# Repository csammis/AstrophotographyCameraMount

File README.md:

# Astrophotography Camera Mount

This project is documented on [Hackaday.io](https://hackaday.io/project/163689-astrophotography-camera-mount)!

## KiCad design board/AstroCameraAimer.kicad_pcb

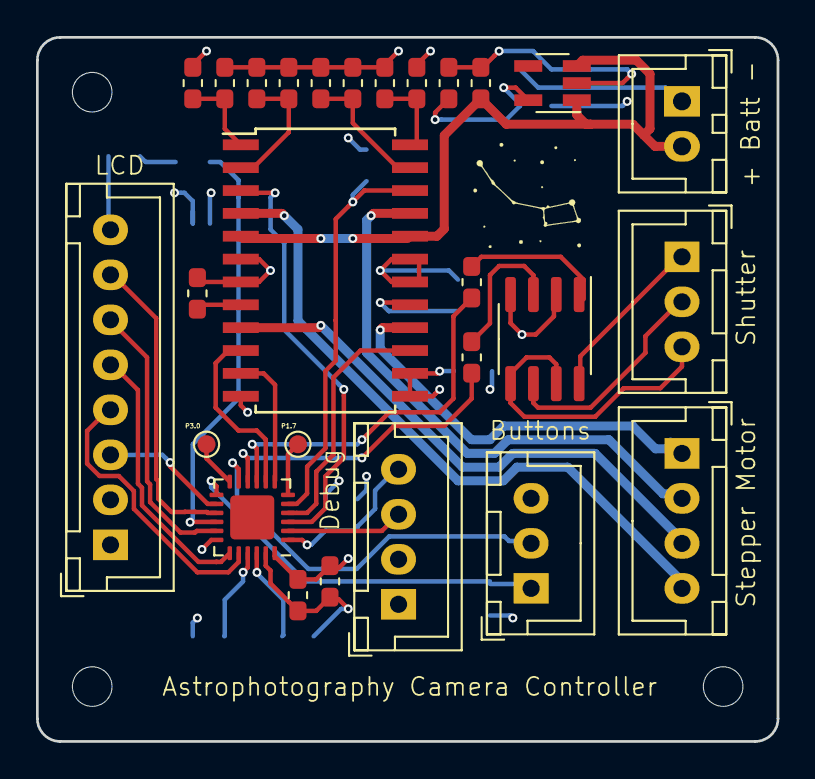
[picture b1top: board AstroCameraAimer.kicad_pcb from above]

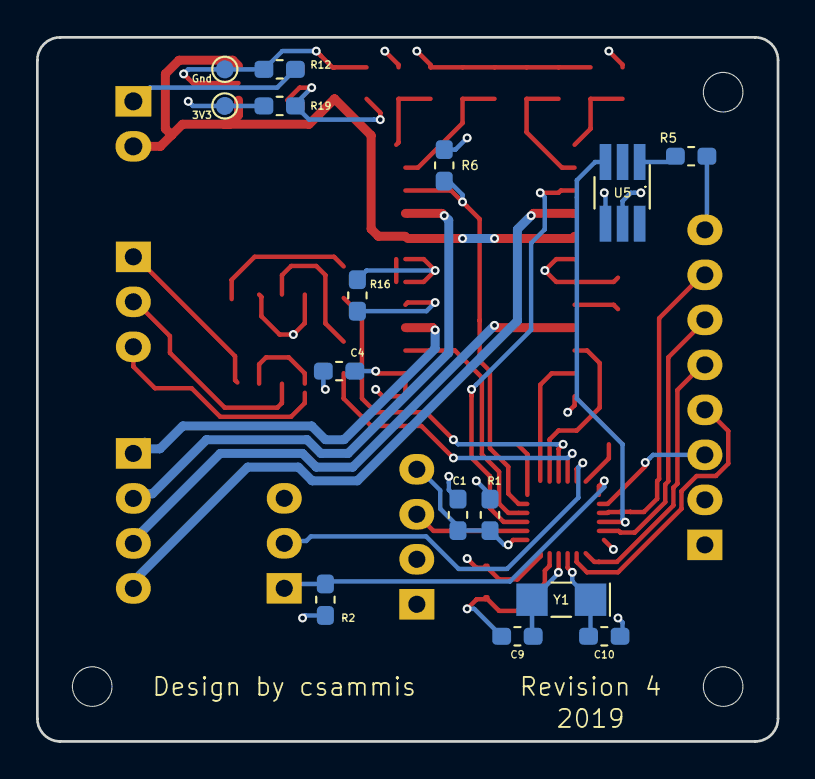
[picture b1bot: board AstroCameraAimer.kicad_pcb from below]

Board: 4 copper layers, 41.1 x 39.1 mm, 46 parts (15 on the bottom side), 43 nets.

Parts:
C1: 1nF; C_0603_1608Metric_Pad1.05x0.95mm_HandSolder
C2: 10uF; C_0603_1608Metric_Pad1.05x0.95mm_HandSolder
C3: 0.1uF; C_0603_1608Metric_Pad1.05x0.95mm_HandSolder
C4, C11, C12: 1uF; C_0603_1608Metric_Pad1.05x0.95mm_HandSolder
C7, C8: 68pF; C_0603_1608Metric_Pad1.05x0.95mm_HandSolder
C9: CL1; C_0603_1608Metric_Pad1.05x0.95mm_HandSolder
C10: CL2; C_0603_1608Metric_Pad1.05x0.95mm_HandSolder
H1, H2, H3: M2; MountingHole_2.2mm_M2
J1: SBW; JST_XH_B04B-XH-A_1x04_P2.50mm_Vertical
J2: Shutter; JST_XH_B03B-XH-A_1x03_P2.50mm_Vertical
J3: LCD; JST_XH_B08B-XH-A_1x08_P2.50mm_Vertical
J4: Battery; JST_XH_B02B-XH-A_1x02_P2.50mm_Vertical
J5: Stepper Motor; JST_XH_B04B-XH-A_1x04_P2.50mm_Vertical
J6: Buttons; JST_XH_B03B-XH-A_1x03_P2.50mm_Vertical
LG1: ProjectLogo; ursa_minor
R1: 47K; R_0603_1608Metric_Pad1.05x0.95mm_HandSolder
R2, R6, R10: 100K; R_0603_1608Metric_Pad1.05x0.95mm_HandSolder
R3, R4, R5: 390; R_0603_1608Metric_Pad1.05x0.95mm_HandSolder
R8: 13K; R_0603_1608Metric_Pad1.05x0.95mm_HandSolder
R9, R15, R20: 20K; R_0603_1608Metric_Pad1.05x0.95mm_HandSolder
R11: 68K; R_0603_1608Metric_Pad1.05x0.95mm_HandSolder
R12, R19: JUMPER; R_0603_1608Metric_Pad1.05x0.95mm_HandSolder
R16, R17: 0.75Ω; R_0603_1608Metric_Pad1.05x0.95mm_HandSolder
TP1: GND; TestPoint_Pad_D1.0mm
TP2: 3.3V; TestPoint_Pad_D1.0mm
TP3: P3.0; TestPoint_Pad_D1.0mm
TP4: P1.7; TestPoint_Pad_D1.0mm
U1: MSP430FR2433; VQFN-24-1EP_4x4mm_P0.5mm_EP2.45x2.45mm
U2: ILD205; SOIC-8_3.9x4.9mm_P1.27mm
U3: A3967; SOIC-24W_7.5x15.4mm_P1.27mm
U4: NCP718; SOT-23-5_HandSoldering
U5: SiP32510; TSOT-23-6_HandSoldering
Y1: 32Khz; Crystal_SMD_MicroCrystal_CC7V-T1A-2Pin_3.2x1.5mm_HandSolder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

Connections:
+3V3: C2.1, C3.2, C4.2, J1.2, J3.1, R1.1, R2.1, R6.1, R8.1, R10.1, R19.1, TP2.1, U1.24, U3.12, U3.13, U3.14, U5.5
/9V_Coil1A: J5.1, U3.16
/9V_Coil1B: J5.2, U3.21
/9V_Coil2A: J5.3, U3.9
/9V_Coil2B: J5.4, U3.4
/LCD_CLK: J3.7, U1.15
/LCD_DC: J3.5, U1.19
/LCD_MOSI: J3.6, U1.17
/LCD_RST: J3.4, U1.20
/LCD_nCS: J3.3, U1.14
BATT_9V: C11.1, J4.2, U3.5, U3.20, U4.1, U4.3
DRIVER_DIR: U1.7, U3.11
DRIVER_STEP: U1.8, U3.10
DRIVER_nENABLE: U1.4, U3.15
DRIVER_nRESET: R6.2, U1.5, U3.22
DRIVER_nSLEEP: U1.3, U3.3
FOCUS: R3.2, U1.9
GND: C1.2, C2.2, C3.1, C4.1, C7.1, C8.1, C9.2, C10.2, C11.2, C12.2, J1.1, J3.2, J6.3, R9.1, R11.2, R12.2, R15.2, R16.1, R17.1, R20.2, TP1.1, U1.18, U1.23, U2.2, U2.4, U3.6, U3.7, U3.18, U3.19, U4.2, U5.4
LCD_LED: U1.16, U5.3
unnamed: C1.1, J1.4, R1.2, U1.1
unnamed: C7.2, R15.1, U3.2
unnamed: C8.2, R20.1, U3.23
unnamed: C9.1, U1.22, Y1.2
unnamed: C10.1, U1.21, Y1.1
unnamed: J1.3, U1.2
unnamed: J2.1, U2.8
unnamed: J2.2, U2.6
unnamed: J2.3, U2.5, U2.7
unnamed: J3.8, R5.1
unnamed: J4.1, R12.1
unnamed: R3.1, U2.1
unnamed: R4.1, U2.3
unnamed: R5.2, U5.1
unnamed: R8.2, R9.2, U3.1
unnamed: R10.2, R11.1, U3.24
unnamed: R16.2, U3.17
unnamed: R17.2, U3.8
unnamed: TP3.1, U1.12
unnamed: TP4.1, U1.6
OK_BTN: J6.1, R2.2, U1.13
SELECT_BTN: J6.2, U1.11
SHUTTER: R4.2, U1.10
SUPPLY_3.3V: C12.1, R19.2, U4.5

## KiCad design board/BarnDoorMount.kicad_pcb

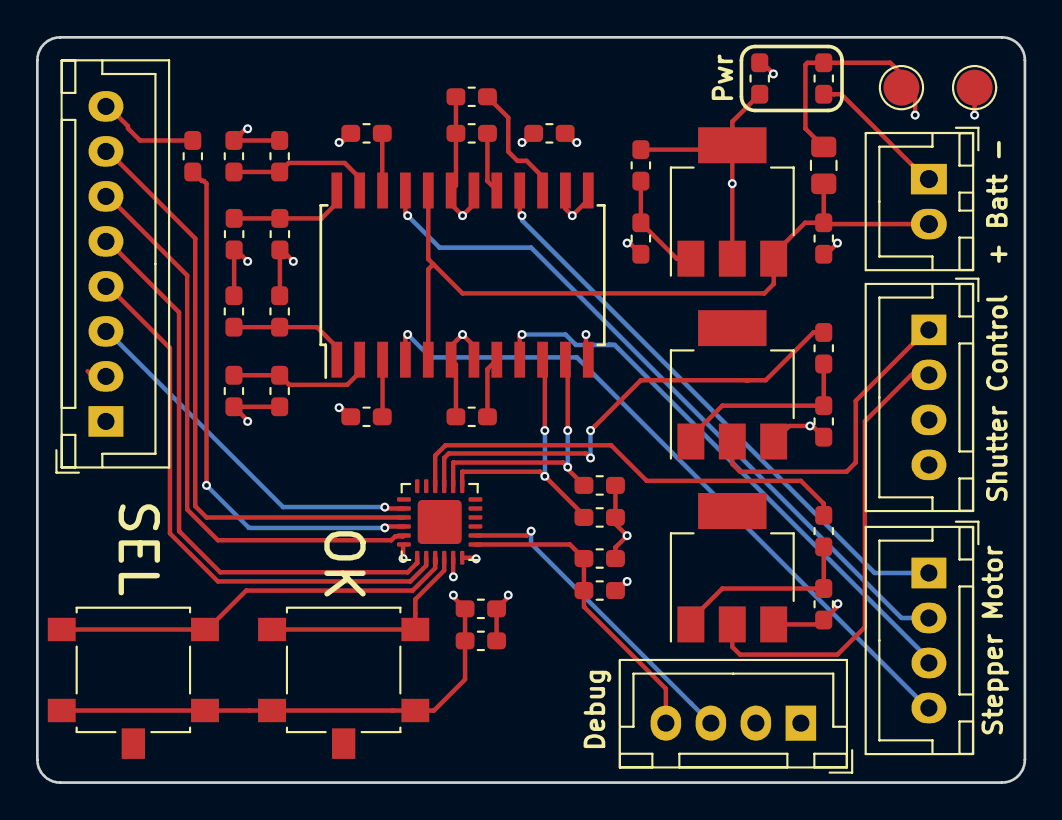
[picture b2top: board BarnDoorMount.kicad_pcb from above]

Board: 4 copper layers, 54.9 x 41.4 mm, 45 parts (0 on the bottom side), 38 nets.

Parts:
+ C5: 47uF; C_0805_2012Metric_Pad1.15x1.40mm_HandSolder
C1: 1nF; C_0603_1608Metric_Pad1.05x0.95mm_HandSolder
C2 +: 10uF; C_0603_1608Metric_Pad1.05x0.95mm_HandSolder
C3, C6: 0.1uF; C_0603_1608Metric_Pad1.05x0.95mm_HandSolder
C4: 1uF; C_0603_1608Metric_Pad1.05x0.95mm_HandSolder
C7, C8: 68pF; C_0603_1608Metric_Pad1.05x0.95mm_HandSolder
J1: SBW; JST_XH_B04B-XH-A_1x04_P2.50mm_Vertical
J2: Shutter Control; JST_XH_B04B-XH-A_1x04_P2.50mm_Vertical
J3: LCD; JST_XH_B08B-XH-A_1x08_P2.50mm_Vertical
J4: Battery; JST_XH_B02B-XH-A_1x02_P2.50mm_Vertical
J5: Stepper Motor; JST_XH_B04B-XH-A_1x04_P2.50mm_Vertical
Q1, Q2: PZT2222A; SOT-223
R1: 47K; R_0603_1608Metric_Pad1.05x0.95mm_HandSolder
R2, R3, R8, R16, R17, R18, R19, R20: 10K; R_0603_1608Metric_Pad1.05x0.95mm_HandSolder
R4, R5: 1K; R_0603_1608Metric_Pad1.05x0.95mm_HandSolder
R6, R11, R15: 20K; R_0603_1608Metric_Pad1.05x0.95mm_HandSolder
R7: 13K; R_0603_1608Metric_Pad1.05x0.95mm_HandSolder
R9: 6.8K; R_0603_1608Metric_Pad1.05x0.95mm_HandSolder
R10, R23: 390; R_0603_1608Metric_Pad1.05x0.95mm_HandSolder
R12, R13: 0.75; R_0603_1608Metric_Pad1.05x0.95mm_HandSolder
R14: 240; R_0603_1608Metric_Pad1.05x0.95mm_HandSolder
R21, R22: JUMPER; R_0603_1608Metric_Pad1.05x0.95mm_HandSolder
SW1: SELECT; SW_SPST_B3S-1100
SW2: OK; SW_SPST_B3S-1100
TP1: TP_GND; TestPoint_Pad_D2.0mm
TP2: TP_33V; TestPoint_Pad_D2.0mm
U1: MSP430FR2433; VQFN-24-1EP_4x4mm_P0.5mm_EP2.45x2.45mm
U2: LM317; SOT-223-3_TabPin2
U3: A3967; SOIC-24W_7.5x15.4mm_P1.27mm

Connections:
+3V3: C2 +.1, C3.2, C4.1, J1.2, J3.1, R1.1, R7.1, R8.1, R18.1, R19.1, R22.1, TP2.1, U1.24, U3.12, U3.13, U3.14
+9V: + C5.1, C6.1, J4.2, U2.3, U3.5, U3.20
FOCUS: R2.2, U1.9
GND: + C5.2, C1.2, C2 +.2, C3.1, C4.2, C6.2, C7.2, C8.2, J1.1, J2.3, J3.2, Q1.3, Q2.3, R4.1, R5.1, R6.1, R9.2, R10.2, R11.2, R12.1, R13.1, R15.2, R16.2, R17.2, R20.1, R21.2, SW1.2, SW2.2, TP1.1, U1.18, U1.23, U3.6, U3.7, U3.18, U3.19
unnamed: C1.1, J1.4, R1.2, U1.1
unnamed: C7.1, R11.1, U3.2
unnamed: C8.1, R15.1, U3.23
unnamed: J1.3, U1.2
unnamed: J2.1, Q1.2
unnamed: J2.2, Q2.2
unnamed: J3.3, U1.14
unnamed: J3.4, U1.20
unnamed: J3.5, U1.19
unnamed: J3.6, U1.17
unnamed: J3.7, U1.15
unnamed: J3.8, R23.2
unnamed: J4.1, R21.1
unnamed: J5.1, U3.16
unnamed: J5.2, U3.21
unnamed: J5.3, U3.9
unnamed: J5.4, U3.4
unnamed: Q1.1, R2.1, R4.2
unnamed: Q2.1, R3.1, R5.2
unnamed: R6.2, R7.2, U3.1
unnamed: R8.2, R9.1, U3.24
unnamed: R10.1, R14.2, U2.1
unnamed: R12.2, U3.17
unnamed: R13.2, U3.8
unnamed: R14.1, R22.2, U2.2
unnamed: R16.1, U1.8, U3.11
unnamed: R17.1, U1.7, U3.10
unnamed: R18.2, U3.3
unnamed: R19.2, U3.22
unnamed: R20.2, U3.15
unnamed: R23.1, U1.16
OK_BTN: SW2.1, U1.22
SELECT_BTN: SW1.1, U1.21
SHUTTER: R3.2, U1.10

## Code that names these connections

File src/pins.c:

#include "pins.h"
#include <msp430.h>

/*-----------------------------------------------
 * Pin Allocations
 *
 * P1.0 DRV GPIO OUTPUT     DRV_DIR
 * P1.1 DRV TA0.1 PWM       Function 10, output
 * P1.2 GPIO OUTPUT         Camera Focus
 * P1.3 GPIO OUTPUT         Camera Shutter
 * P1.4
 * P1.5
 * P1.6
 * P1.7 DRV GPIO OUTPUT     DRV_DIR
 * P2.0 BTN GPIO INPUT      Select Button
 * P2.1 BTN GPIO INPUT      Okay Button
 * P2.2
 * P2.3
 * P2.4 LCD UCA1 SPI SCLK   Function 01
 * P2.5 LCD GPIO OUTPUT     LCD LED
 * P2.6 LCD UCA1 SPI SIMO   Function 01
 * P2.7 LCD GPIO OUTPUT     LCD_DC
 * P3.0
 * P3.1 LCD UCA1 SPI STE    Function 01
 * P3.2 LCD GPIO OUTPUT     LCD_RST
 *
-----------------------------------------------*/

#define PORT1_DIR       (BIT0 | BIT1 | BIT2 | BIT3 | BIT7)
#define PORT2_DIR       (BIT5 | BIT7)
#define PORT3_DIR       (BIT2)

#define PORT1_SEL0      (  0  |   0  |   0  |   0  |   0  |   0  |   0  |   0 )
#define PORT1_SEL1      (  0  | BIT1 |   0  |   0  |   0  |   0  |   0  |   0 )

#define PORT2_SEL0      (  0  |   0  |   0  |   0  | BIT4 |   0  | BIT6 |   0 )
#define PORT2_SEL1      (  0  |   0  |   0  |   0  |   0  |   0  |   0  |   0 )

#define PORT3_SEL0      (  0  | BIT1 |   0 )
#define PORT3_SEL1      (  0  |   0  |   0 )

void init_pins(void)
{
    // Set pin directions and mux selections
    P1DIR   = PORT1_DIR;
    P2DIR   = PORT2_DIR;
    P3DIR   = PORT3_DIR;

    P1SEL0  = PORT1_SEL0;
    P1SEL1  = PORT1_SEL1;
    P2SEL0  = PORT2_SEL0;
    P2SEL1  = PORT2_SEL1;
    P3SEL0  = PORT3_SEL0;
    P3SEL1  = PORT3_SEL1;

    // Finally, unlock the default high-impedance state and set current configurations
    PM5CTL0 &= ~LOCKLPM5;
}

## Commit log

2018-03-04 Sensor driver functioning, XL is nothing but zeros though
2018-03-04 Added .gitignore
2018-03-04 Added stepper motor driver...driver
2018-03-30 Updated PWM_PERIOD to correct value for the ver 0.1 mechanics
2018-04-20 Fixed up the i2c driver and sensor reads
2018-05-05 Updated the LCD driver to be interrupt-based
2018-05-05 Adding dependency on QmathLib to handle fixed point arithmetic and trig
2018-05-07 Remove sensor enable pin, added GPS pin to definition
2018-05-07 Exercise positioning code
2018-05-07 *commit* positioning code
2018-05-22 Implemented a timer loop to handle basic periodic events
2018-05-22 Fleshed out GPS interface and added fake data for testing
2018-07-22 Refactored charset to be accessed from multiple object files
2018-07-22 Changing sensor type to _iq16 for better precision
2018-07-22 Update UI after GPS fix to show current heading
2018-07-26 Work on cleaning up the sensor input scaling
2018-11-19 Temporarily removing the sensor array - will be permanent
2018-11-19 Initial commit of driver board
2018-11-19 OpenSCAD files for the gear train
2018-12-22 Revision 2 of the driver board
2018-12-22 Lots of changes for revision 2
    * Removed sensors
    * Removed GPS
    * Added buttons
    * Added a menu system
2019-02-04 Replace gear_assembly.scad with planetary gear train design
2019-02-04 Software changes for rev 3: menu options for speed and timer, PWM timing for speeds, delightful graphics for sidereal rate
2019-02-04 Board changes for rev 3: swap STEP and DIR pins between the MCU and stepper driver
2019-02-04 Renamed the board files since this is not a barndoor mount anymore
2019-02-04 Remove QMathLib from build
2019-02-13 Added a tripod mount and camera ball head attachments
2019-02-13 Implemented a "Gearbox Test" speed to drive the motor fast enough to see motion at the end
2019-06-28 Updated schematic and PCB to revision 3
2019-07-18 Consolidating local symbol libraries
2019-07-18 Removing stray file from old project naming scheme
2019-07-18 Removing another stray file
2019-08-23 Fix NCP718 footprint and update board to revision 4
2019-08-23 Adding a README, finally
